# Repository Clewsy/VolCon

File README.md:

# volcon

A USB volume controller that uses a VCR head drum for the knob.

More photos and information can be found [here][link_clews_volcon].

Proudly mentioned at [hackaday.com][link_web_hackaday_volcon], and also on [episode 106][link_web_hackaday_podcast_106] of the [hackaday podcast][link_web_hackaday_podcast].

## Revision 1

This project began as an experiment when I wanted to learn how an optical [quadrature encoder][link_web_quadrature_encoder] worked (FYI, 2-bit [Gray code][link_web_gray_code]).

It transformed into a learning experience around USB - specifically the [HID protocol][link_web_hid].  Ultimately I ended up with a simple gadget that now sits on my desk and allows me to control the PC volume.

A salvaged optical encoder was used to detect rotation along with a reclaimed [head drum][link_web_head_drum] from a [VCR][link_web_vcr] which was repurposed as a control knob. I very much like the smooth bearings combined with the heavy mass that let the drum spin forever.

Key concepts for the project were:

* The optical encoder parts (sensors and disk) were salvaged from an old track-ball.
* The "knob" was made from the head drum of a VHS VCR (remember those?). This is the part that spins and is used to adjust volume on my PC.
* This assembly is mounted to a custom PCB with some nylon stand-offs. The PCB became the base of the whole unit.
* The optical disk was fixed to the shaft and optical sensors mounted to one of the nylon standoffs.
* I cut some wooden rings to enclose the electronics and the base of the VCR drum.
* The original custom PCB was designed in eagle and etched at home from some single-sided copper-clad board. The circuit was designed around an AVR AT90usb162.
* The code is written in C and implements the LUFA library developed by Dean Camera.
* The whole unit plugs into a PC via USB and is automatically identified as a HID - no drivers required (tested in Debian, Ubuntu and Windows).
* It's a very simple device - rotate clockwise to increase volume, counter-clockwise to decrease.

I used the [LUFA][link_web_lufa] (lightweight USB Framework for AVRs) library to implement the USB HID protocol.

After some time (about six years!) of having this device in-use on my desk, I got sick of the simple (ugly) stained pine wood enclosure. With some scrap spotted gum and a router (with a Roman ogee and a roundover bit) I made a slightly nicer enclosure for volcon.

## Revision 2

After even more time, I gave the project an overhaul. Revision 2 uses the same head drum, optical encoder sensors and wooden enclosure. The upgrades from revision 1 include:
* Schematic and PCB layout completely redone but using [KiCad][link_web_kicad] instead of Eagle.
* Microcontroller changed from an AT90usb162 AVR to an ATmega32U4 (simply because I have a few of these).
* Remove the serial Tx/Rx connector (only used this for debugging revision 1).
* Remove the reset tact-switch (also was only used when debugging).
* Use smd components instead of through-hole.
* Connect with a USB type-C connector instead of a USB type-B.
* Have the PCB fabricated (JLCPCB) instead of the home-made copper-etch method.
* A couple of LEDs on the bottom of the PCB purely to visualise the gray code (revision 1 had LEDs, but they only barely shone through etched sections of the PCB).
* Generally improved and cleaner code (still using the LUFA library).

## Revision 2.1

I've been experimenting with 3D prints so I designed and printed a "cap" for the volume controller.  Designed in [freecad][link_web_freecad], printed on a [Prusa CORE One+][link_web_prusa].  CAD files are [here][link_repo_volcon_cap].

![volcon with a 3D-printed cap.][link_image_volcon_cap]
![The completed volcon.][link_image_volcon]

[link_image_volcon]:volcon.jpg
[link_image_volcon_cap]:hardware/cap/volcon_cap.jpg

[link_clews_volcon]:https://clews.pro/projects/volcon.php

[link_repo_volcon_cap]:/hardware/cap/

[link_web_freecad]:https://www.freecad.org/
[link_web_gray_code]:https://en.wikipedia.org/wiki/Gray_code
[link_web_hackaday_podcast]:https://hackaday.com/category/podcasts/
[link_web_hackaday_podcast_106]:https://hackaday.com/2021/02/19/hackaday-podcast-106-connector-kerfuffle-tuning-fork-time-spinach-contact-prints-and-teslas-permanent-memory/
[link_web_hackaday_volcon]:https://hackaday.com/2021/02/15/a-volume-control-from-a-vcr-drum/
[link_web_head_drum]:https://en.wikipedia.org/wiki/File:Kopftrommel_2.jpg
[link_web_hid]:https://en.wikipedia.org/wiki/USB_human_interface_device_class
[link_web_kicad]:https://www.kicad.org/
[link_web_lufa]:http://fourwalledcubicle.com/LUFA.php
[link_web_prusa]:https://www.prusa3d.com/
[link_web_quadrature_encoder]:https://en.wikipedia.org/wiki/Quadrature_encoder
[link_web_vcr]:https://en.wikipedia.org/wiki/Videocassette_recorder

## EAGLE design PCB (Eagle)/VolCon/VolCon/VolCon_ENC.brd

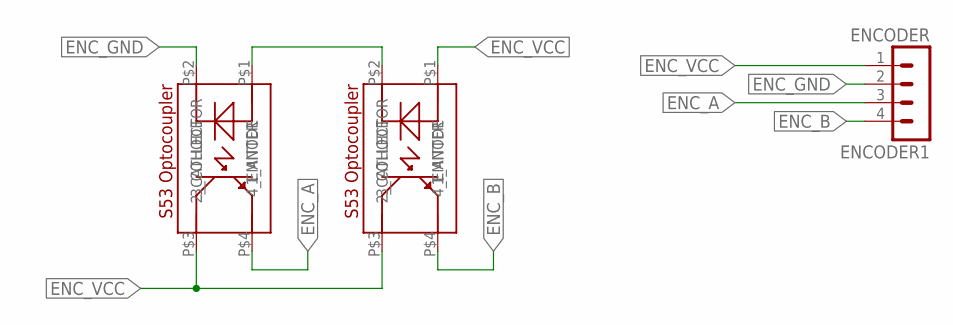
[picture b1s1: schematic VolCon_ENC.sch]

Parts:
ENCODER1: ENCODER; MA04-1
U$3, U$4: SHARP_S53

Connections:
ENC_A: ENCODER1.3, U$4.P$4 (4_EMITTER)
ENC_B: ENCODER1.4, U$3.P$4 (4_EMITTER)
ENC_GND: ENCODER1.2, U$4.P$2 (2_CATHODE)
ENC_VCC: ENCODER1.1, U$3.P$1 (1_ANODE), U$3.P$3 (3_COLLECTOR), U$4.P$3 (3_COLLECTOR)
unnamed: U$3.P$2 (2_CATHODE), U$4.P$1 (1_ANODE)

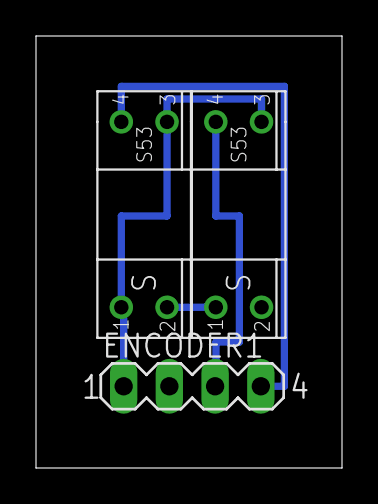
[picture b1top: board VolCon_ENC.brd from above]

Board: 2 copper layers, 17.0 x 24.0 mm, 3 parts (0 on the bottom side), 5 nets.

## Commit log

2021-01-26 Beginning a second revision.
2021-01-26 Compressed earlier revision.
2021-01-26 Ignore exported gerber files.
2021-01-26 Transistor datasheet.
2021-01-27 Datasheets.
2021-01-28 Crystal datasheet.
2021-02-06 Hobbled code together from other projects. Basic functionality working, time to clean it up.
2021-02-06 Clean-up and efficiencies.
2021-02-06 Code is in pretty good shape.
2021-02-07 Minor adjustments, clean-up and comments. Generated schematic pdf for repo.
2021-02-11 Readme and photo.
2021-02-11 Embed photo in readme.
2021-02-12 Fixed some comment typos and tidied some code for readability.
2021-02-13 Add vscode c_cpp_propoerties to repo - better intellisense results.
2021-02-21 Revised readme. Added links to hackaday article and hackaday podcast.
2026-06-20 3d-printed cap
